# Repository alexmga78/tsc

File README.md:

# Engineering Validation (EVT) - PCB and Mechanical Design

## Project Overview

This project focuses on the design and validation of a printed circuit board (PCB) for an electronic device that includes various components like an ESP32-C6 module, battery, display, and mechanical housing. The goal is to ensure that the PCB fits within the given mechanical enclosure, adheres to specified electrical and mechanical constraints, and follows best practices for power routing, component placement, and design rules.

## Project Structure

- **Hardware**
  - **Schematic File** (`.sch`)
  - **PCB Layout File** (`.brd`)
- **Manufacturing**
  - **Gerbers** (`gerbers.zip`)
  - **Bill of Materials** (`.bom`)
  - **Pick and Place File** (`.cpl`)
- **Mechanical**
  - **3D Model of Complete Device** (exploded view `.step`)
  - **Fusion 360 3D Model** (assembled device)
- **Images**
  - Renders of the device, PCB, and individual components
- **LICENSE**
  - License information
- **README.md**
  - This file, describing the project

## Design Decisions and Functional Overview

### 1. **Schematic Design**
The schematic was designed according to the provided model and constraints. Key considerations included ensuring proper placement of decoupling capacitors close to the power pins of critical components, maintaining correct power and data routing widths, and keeping signal integrity intact.

- **Power Routing**: Power traces were routed with a minimum width of `0.3mm` for power rails (e.g., VCC, VBUS) and `0.15mm` for signal traces.
- **Component Placement**: All components were placed on the **TOP** layer of the PCB, with key modules grouped around the central ESP32-C6 microcontroller. The placement adhered to the mechanical dimensions of the housing.
- **Stacked Ground Planes**: Ground planes were created both on the **TOP** and **BOTTOM** layers, and via stitching was applied near the ESP32 module to ensure minimal noise.

### 2. **PCB Layout and Constraints**
Following the provided layout file, I ensured the PCB design adhered to all mechanical and electrical constraints, including:
- **Fitment with Housing**: The PCB was designed to fit inside the provided mechanical enclosure, and critical components such as buttons and USB connectors were positioned as per the specified dimensions.
- **ESP32 Antenna**: The antenna of the ESP32 module was placed near the outer edge of the PCB, and the area beneath it was cut out to minimize interference with the radio signal.
- **Double-sided Routing**: While routing was done on both the **TOP** and **BOTTOM** layers, I avoided vias on power traces and ensured that no signals were routed under the ESP32 antenna.
  
### 3. **Gerber Files**
Gerber files were generated to provide the necessary information for PCB manufacturing. I used the standard process outlined in the provided tutorial to generate the following:
- **Gerber Files** for PCB manufacturing
- **Bill of Materials** (BOM) for procurement
- **Pick and Place File** for component placement during assembly

### 4. **Mechanical Model**
The 3D model of the complete device, including the PCB, battery, display, and housing, was created in Fusion 360. The exploded view `.step` file shows the assembly process and how the components fit within the housing. The models for the battery and display were drawn according to their respective datasheets to ensure accurate dimensions.

- **Battery and Display Integration**: The battery was directly connected to the PCB's test pads, and the display was integrated according to its specified connections.

## Design Rule Check (DRC) and Electrical Rule Check (ERC)

The design was thoroughly checked using the DRC and ERC files provided in the project resources. All electrical and mechanical design constraints were respected, and the following issues were resolved:
- **Power trace widths** and **component placement** were validated.
- **Test pads** were clearly marked in the silkscreen layer with their corresponding signal names (e.g., MISO, MOSI, GND).
- **Via stitching** was applied to ensure proper grounding, particularly around the ESP32 module.

### 5. **Components Used in Mechanical and Electrical Integration**

The following key components were integrated into the design, both electrically on the PCB and mechanically within the Fusion 360 model. Each part was selected based on its functionality, size constraints, and compatibility with the ESP32-C6 ecosystem.

#### **Microcontroller Unit (MCU)**
- **ESP32-C6-WROOM-1-N1 (U2)**  
  A high-performance wireless module with integrated Wi-Fi and Bluetooth LE capabilities. This module acts as the central processing unit, managing connectivity, data handling, and control tasks for the entire device.

#### **Power Supply and Management**
- **USB-C Connector**  
  Primary power input for the device, allowing both power delivery and data communication.
- **LDO Voltage Regulator – XC6220A331MR-G (IC4)**  
  Ensures stable voltage for sensitive components, converting input power to regulated 3.3V.
- **Battery Charging IC – MCP73831**  
  Handles safe charging of a single-cell Li-Po battery, enabling portable operation.
- **Fuel Gauge – MAX17048G+T10 (U4)**  
  Monitors battery voltage and provides state-of-charge estimation for accurate power management.

#### **Memory and Data Storage**
- **External NOR Flash – W25Q512JVEIQ (U1)**  
  Non-volatile memory used to store logs, firmware updates, or configuration data.
- **MicroSD Card Slot**  
  Provides removable storage capability, useful for storing larger datasets or logs.

#### **Real-Time Clock (RTC)**
- **RTC Module – DS3231SN (U3)**  
  Maintains accurate timekeeping, even during power loss. A supercapacitor (C10) is included to retain time data temporarily when external power is disconnected.

#### **Environmental Sensing**
- **BME688 Sensor**  
  Measures temperature, humidity, pressure, and gas, providing rich environmental data for various applications.

#### **User Interface**
- **E-Paper Display**  
  A low-power screen for displaying information clearly and efficiently. Connected via a flat flex connector (`FH34SR-24S-0.5SH_99`) and supported by driver circuitry on the PCB.
- **Buttons (Boot, Reset, Change)**  
  Physical interface elements allowing users to interact with the system, perform resets, or trigger mode changes.

#### **Communication Interfaces**
- **Wireless Connectivity via ESP32-C6**  
  Native support for Wi-Fi 6 and Bluetooth LE enables fast, efficient communication with external devices or networks.

#### **Protection and Debugging**
- **ESD Protection – USBLC6-2SC6Y, PEMF050.1**  
  Safeguards sensitive components against electrostatic discharge from USB or other user-accessible interfaces.
- **Test Pads**  
  Strategically placed signal pads facilitate in-circuit testing and debugging during development or production.

#### **Expandability**
- **Qwiic/Stemma QT Connector**  
  Provides a plug-and-play I2C expansion port for easily integrating additional sensors or peripherals.

### 6. **MCU ESP32 Pins**

The ESP32-C6-WROOM-1 module was integrated as the core processing and communication unit. Its pinout was utilized to support a range of subsystems within the device. The following is an overview of how specific pins were used and organized in the design:

#### **Antenna Placement**
The ESP32-C6 features an integrated PCB antenna located at the end of the module. In this design, the antenna was placed along the outer edge of the PCB to maximize RF performance. A cutout was added beneath the antenna to reduce signal interference from copper traces or ground planes, ensuring reliable wireless communication.

#### **Power Pins**
- `3V3` and `GND` pins were used to supply and stabilize power to the ESP32 module.
- Proper decoupling capacitors were placed near these pins to minimize voltage fluctuations.

#### **USB Communication**
- USB data lines (`D+`, `D−`) were routed to the USB-C connector through ESD protection components, enabling USB-based programming and power delivery.

#### **SD Card Interface**
- Pins such as `CMD`, `CLK`, and `DAT0–DAT2` were connected to the MicroSD card slot to support external storage over an SDIO interface.

#### **SPI Communication**
- The SPI bus (`CS`, `SCK`, `MOSI`, `MISO`) was connected to the external flash memory (W25Q512JVEIQ) for fast, non-volatile storage access.

#### **I2C Bus**
- Two dedicated pins (`SDA`, `SCL`) were used to establish I2C communication with peripherals like the RTC (DS3231SN), environmental sensor (BME688), and the Qwiic/Stemma QT expansion port.

#### **GPIO Usage**
- Multiple GPIOs were assigned to handle:
  - **User Inputs**: Buttons such as Boot, Reset, and Change.
  - **Display Control**: Interface signals for driving the E-Paper display.
  - **Debug/Test Access**: Certain unused GPIOs were routed to test pads for development and troubleshooting.

All unused or unassigned GPIOs were kept accessible where possible for future flexibility.

## Issues and Resolutions

During the design and validation process, the following issues were identified and addressed:
- **Issue**: Minor overlap errors in component placement near the USB and button area.
  - **Resolution**: These errors were ignored as per the project instructions, as they did not interfere with functionality or the overall fit of the components inside the housing.
- **Issue**: Antenna placement under components.
  - **Resolution**: The PCB was redesigned to ensure no components or traces were placed beneath the antenna, and the area was cut out as required.

## Conclusion

This project adheres to the design specifications provided, ensuring that all hardware components, such as the ESP32-C6, battery, display, and PCB, fit within the specified mechanical enclosure. The design respects electrical and mechanical constraints, ensuring proper functionality, ease of assembly, and minimal interference.

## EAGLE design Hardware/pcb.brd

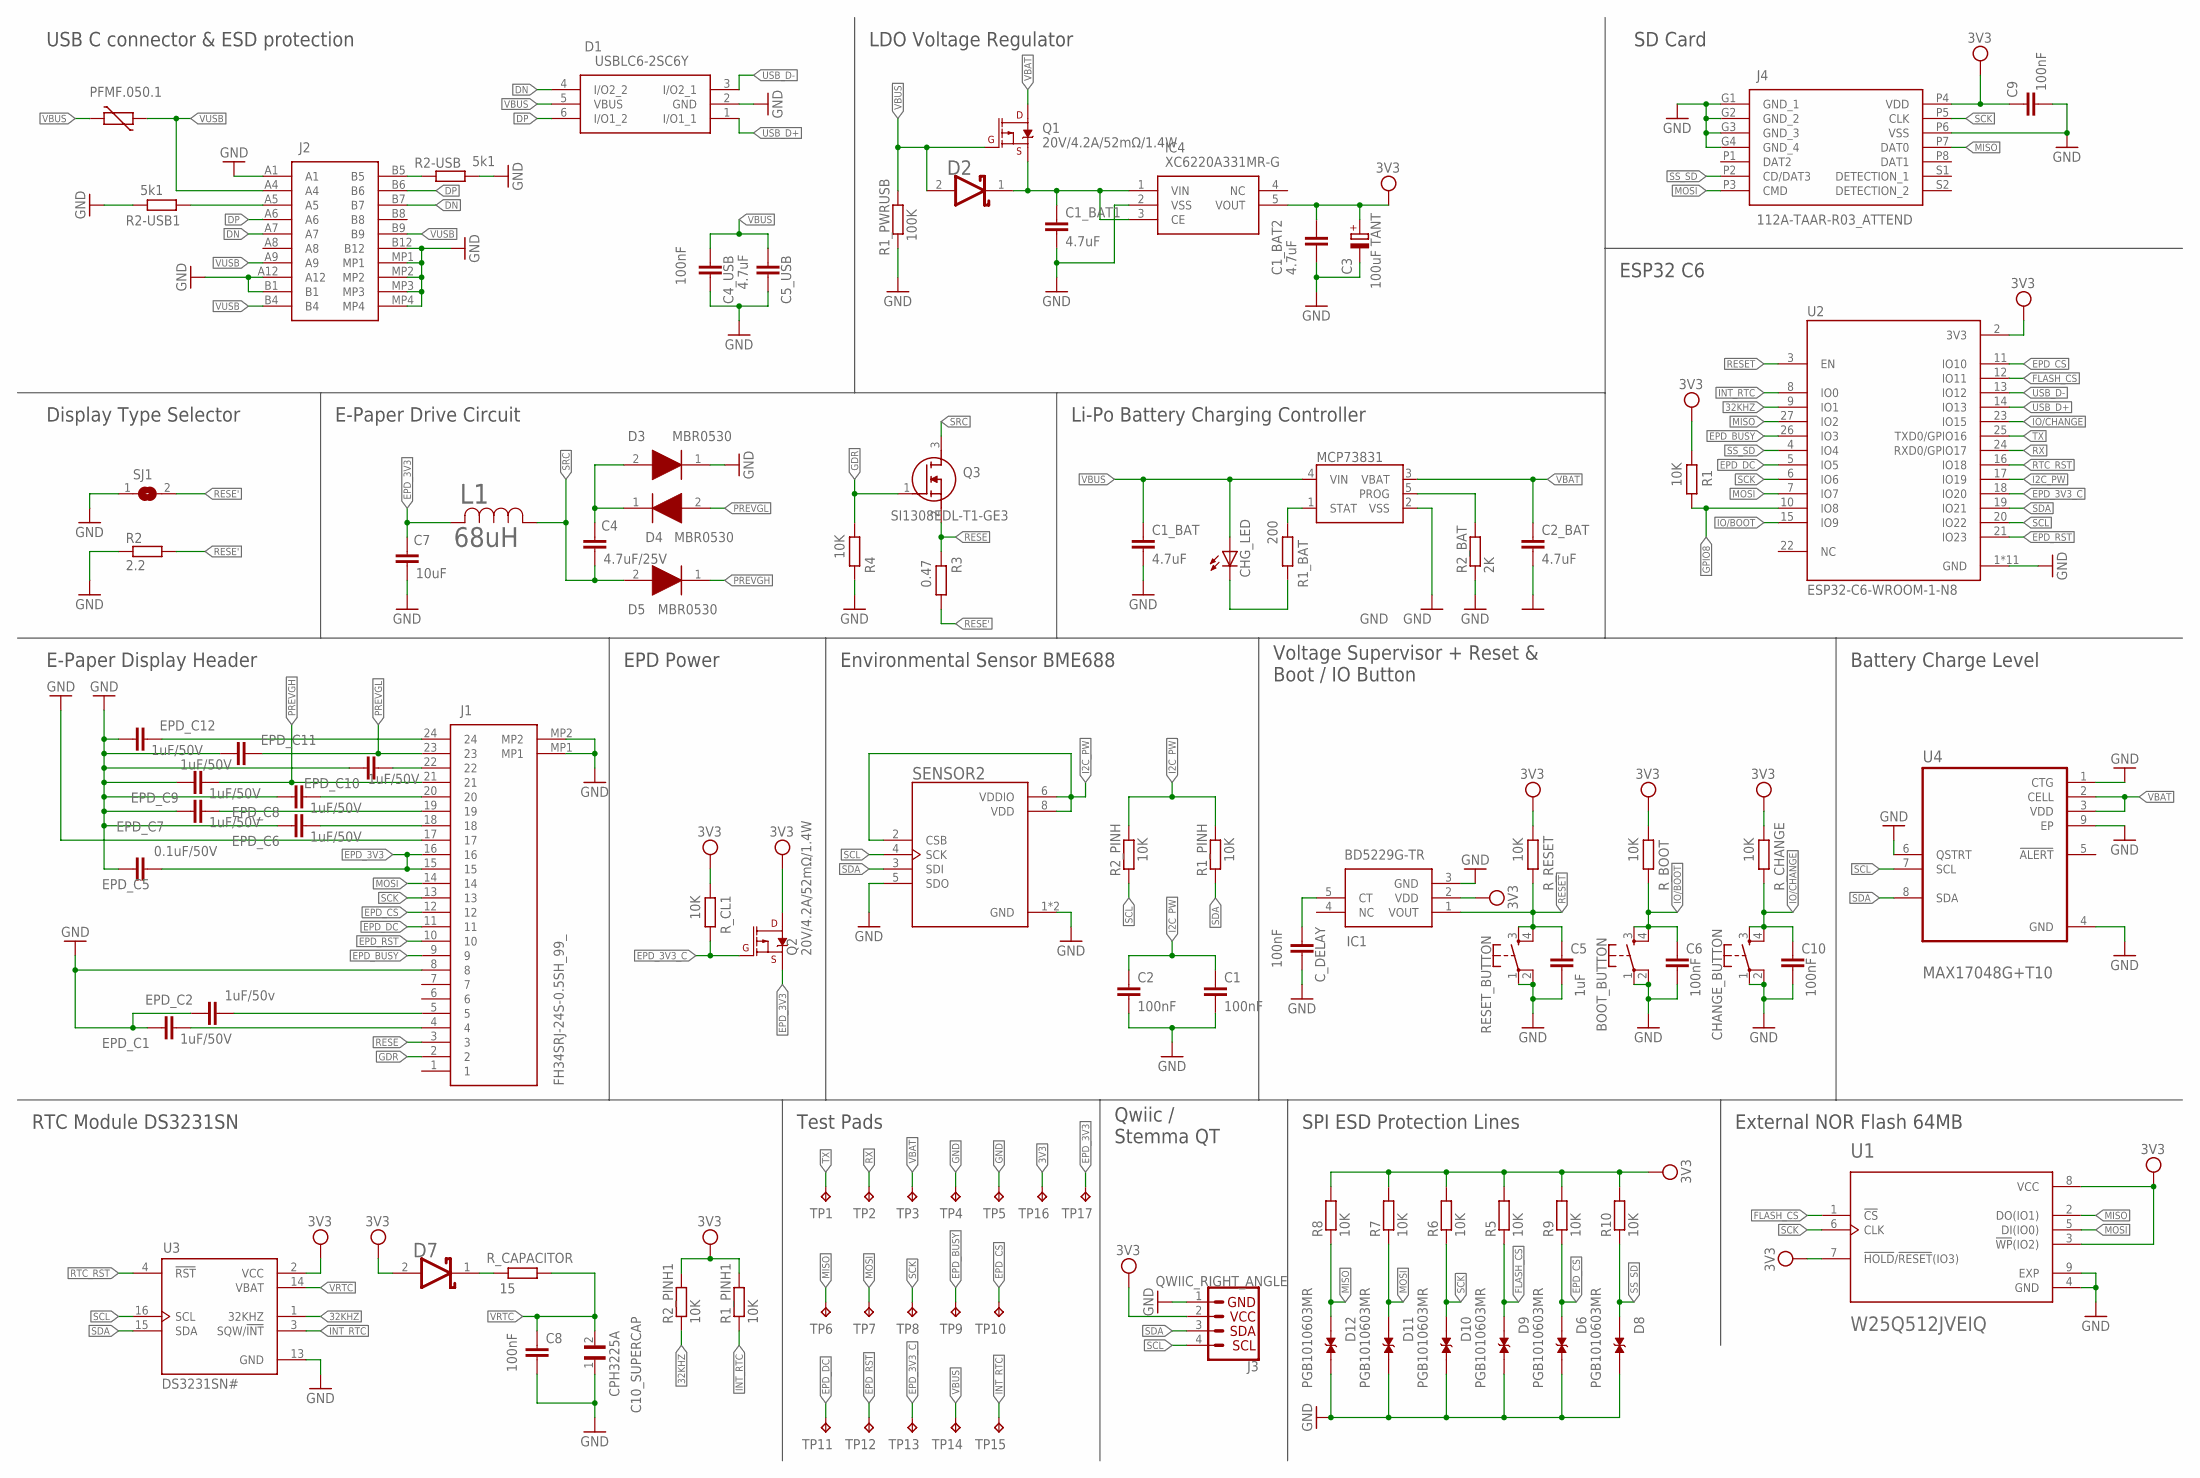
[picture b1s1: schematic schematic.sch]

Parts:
BOOT_BUTTON: BUTTON_CUSYOMV1; MYBUTTON
C1, C2, C6, C8, C9, C10: 100nF; ESP32_WROVER_EAGLE-LTSPICE_C0402
C1_BAT, C1_BAT1, C1_BAT2, C2_BAT: 4.7uF; ESP32_WROVER_EAGLE-LTSPICE_C0402
C3: 100uF TANT; RCL_CT3528
C4: 4.7uF/25V; EAGLE-LTSPICE_C0402
C4_USB: 100nF; EAGLE-LTSPICE_C0402
C5: 1uF; ESP32_WROVER_EAGLE-LTSPICE_C0402
C5_USB: 4.7uF; EAGLE-LTSPICE_C0402
C7: 10uF; EAGLE-LTSPICE_C0402
C10_SUPERCAP: CPH3225A; CAPCP3225X100N
CHANGE_BUTTON: BUTTON_CUSYOMV1; MYBUTTON
CHG_LED: ADAFRUIT_LEDCHIP-LED0603; ADAFRUIT_CHIP-LED0603
C_DELAY: 100nF; ESP32_WROVER_EAGLE-LTSPICE_C0402
D1: USBLC6-2SC6Y; SOT95P280X145-6N
D2, D7: ESP32_WROVER_AVX---SD0805S020S1R0_AVX_SD0805S020S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; ESP32_WROVER_AVX---SD0805S020S1R0_AVX_SD0805S020S1R0_0
D3, D4, D5: MBR0530; SOD3716X135N
D6, D8, D9, D10, D11, D12: PGB1010603MR; DIOC1608X36N
EPD_C1, EPD_C6, EPD_C7, EPD_C8, EPD_C9, EPD_C10, EPD_C11, EPD_C12: 1uF/50V; EAGLE-LTSPICE_C0402
EPD_C2: 1uF/50v; EAGLE-LTSPICE_C0402
EPD_C5: 0.1uF/50V; EAGLE-LTSPICE_C0402
IC1: BD5229G-TR; SOT95P280X125-5N
IC4: XC6220A331MR-G; SOT95P280X120-5N
J1: FH34SRJ-24S-0.5SH_99_; FH34SRJ24S05SH99
J2: SAMACSYS_PARTS_USB4110-GF-A; SAMACSYS_PARTS_USB4110GFA
J3: QWIIC_RIGHT_ANGLE; JST04_1MM_RA
J4: 112A-TAAR-R03_ATTEND; 112ATAARR03ATTEND
L1: 68uH; IND_4828-WE-TPC_WRE
MCP73831: ESP32_WROVER_SPARKFUN-IC-POWER_MCP73831; ESP32_WROVER_SPARKFUN-IC-POWER_SOT23-5
PFMF.050.1: ESP32C6_VARISTORCN1812; ESP32C6_VARISTOR_CT/CN1812
Q1, Q2: 20V/4.2A/52mΩ/1.4W; ESP32_WROVER_SPARKFUN-DISCRETESEMI_SOT23-3
Q3: SI1308EDL-T1-GE3; SOT65P210X110-3N
R1, R1_PINH, R1_PINH1, R2_PINH, R2_PINH1, R4, R5, R6, R7, R8, R9, R10: 10K; ESP32_WROVER_EAGLE-LTSPICE_R0402
R1_BAT: 200; ESP32_WROVER_EAGLE-LTSPICE_R0402
R1_PWRUSB: 100K; ESP32_WROVER_EAGLE-LTSPICE_R0402
R2: 2.2; ESP32_WROVER_EAGLE-LTSPICE_R0402
R2-USB, R2-USB1: 5k1; ESP32_WROVER_EAGLE-LTSPICE_R0402
R2_BAT: 2K; ESP32_WROVER_EAGLE-LTSPICE_R0402
R3: 0.47; ESP32_WROVER_EAGLE-LTSPICE_R0402
RESET_BUTTON: BUTTON_CUSYOMV1; MYBUTTON
R_BOOT: 10K; ESP32_WROVER_EAGLE-LTSPICE_R0402
R_CAPACITOR: 15; ESP32_WROVER_EAGLE-LTSPICE_R0402
R_CHANGE: 10K; ESP32_WROVER_EAGLE-LTSPICE_R0402
R_CL1: 10K; ESP32_WROVER_EAGLE-LTSPICE_R0402
R_RESET: 10K; ESP32_WROVER_EAGLE-LTSPICE_R0402
SENSOR2: ESP32_WROVER_BME680_BME680; ESP32_WROVER_BME680_PSON80P300X300X100-8N
SJ1: SJ
TP1, TP2, TP3, TP4, TP5, TP6, TP7, TP8, TP9, TP10, TP11, TP12, TP13, TP14, TP15, TP16, TP17: TPTP20R; TP20R
U1: W25Q512JVEIQ; SON127P600X800X80-9N
U2: ESP32-C6-WROOM-1-N8; XCVR_ESP32-C6-WROOM-1-N8
U3: DS3231SN#; SOIC127P1032X265-16N
U4: MAX17048G+T10; SON50P200X200X80-9N

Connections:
3V3: C1_BAT2.1, C3.+, C9.1, D7.2 (ANODE), IC1.2 (VDD), IC4.5 (VOUT), J3.2, J4.P4 (VDD), Q2.3 (D), R1.2, R1_PINH1.2, R2_PINH1.2, R5.2, R6.2, R7.2, R8.2, R9.2, R10.2, R_BOOT.2, R_CHANGE.2, R_CL1.2, R_RESET.2, TP16.TP, U1.3 (!WP!(IO2)), U1.7 (!HOLD!/!RESET!(IO3)), U1.8 (VCC), U2.2 (3V3), U3.2 (VCC)
32KHZ: R2_PINH1.1, U2.9 (IO1), U3.1 (32KHZ)
DN: D1.4 (I/O2_2), J2.A7, J2.B7
DP: D1.6 (I/O1_2), J2.A6, J2.B6
EPD_3V3: C7.1, EPD_C5.2, J1.15, J1.16, L1.2, Q2.2 (S), TP17.TP
EPD_3V3_C: Q2.1 (G), R_CL1.1, TP13.TP, U2.18 (IO20)
EPD_BUSY: J1.9, TP9.TP, U2.26 (IO3)
EPD_CS: D6.1, J1.12, R9.1, TP10.TP, U2.11 (IO10)
EPD_DC: J1.11, TP11.TP, U2.5 (IO5)
EPD_RST: J1.10, TP12.TP, U2.21 (IO23)
FLASH_CS: D9.1, R5.1, U1.1 (!CS), U2.12 (IO11)
GDR: J1.2, Q3.1 (G), R4.2
GND: BOOT_BUTTON.1, BOOT_BUTTON.2, C1.2, C1_BAT.2, C1_BAT1.2, C1_BAT2.2, C2.2, C2_BAT.2, C3.-, C4_USB.2, C5.2, C5_USB.2, C6.2, C7.2, C8.2, C9.2, C10.2, C10_SUPERCAP.1, CHANGE_BUTTON.1, CHANGE_BUTTON.2, C_DELAY.2, D1.2 (GND), D3.1 (K), D6.2, D8.2, D9.2, D10.2, D11.2, D12.2, EPD_C1.1, EPD_C2.1, EPD_C5.1, EPD_C6.1, EPD_C7.1, EPD_C8.1, EPD_C9.1, EPD_C10.1, EPD_C11.1, EPD_C12.1, IC1.3 (GND), IC4.2 (VSS), J1.8, J1.17, J1.MP1, J1.MP2, J2.A1, J2.A12, J2.B1, J2.B12, J2.MP1, J2.MP2, J2.MP3, J2.MP4, J3.1, J4.G1 (GND_1), J4.G2 (GND_2), J4.G3 (GND_3), J4.G4 (GND_4), J4.P6 (VSS), MCP73831.2 (VSS), R1_PWRUSB.1, R2.1, R2-USB.2, R2-USB1.1, R2_BAT.1, R4.1, RESET_BUTTON.1, RESET_BUTTON.2, SENSOR2.1 (GND), SENSOR2.5 (SDO), SENSOR2.7 (GND), SJ1.1, TP4.TP, TP5.TP, U1.4 (GND), U1.9 (EXP), U2.1 (GND), U2.28 (GND), U2.29_1 (GND), U2.29_2 (GND), U2.29_3 (GND), U2.29_4 (GND), U2.29_5 (GND), U2.29_6 (GND), U2.29_7 (GND), U2.29_8 (GND), U2.29_9 (GND), U3.13 (GND), U4.1 (CTG), U4.4 (GND), U4.6 (QSTRT), U4.9 (EP)
GPIO8: R1.1, U2.10 (IO8)
I2C_PW: C1.1, C2.1, R1_PINH.2, R2_PINH.2, SENSOR2.2 (CSB), SENSOR2.6 (VDDIO), SENSOR2.8 (VDD), U2.17 (IO19)
INT_RTC: R1_PINH1.1, TP15.TP, U2.8 (IO0), U3.3 (SQW/!INT)
IO/BOOT: BOOT_BUTTON.3, BOOT_BUTTON.4, C6.1, R_BOOT.1, U2.15 (IO9)
IO/CHANGE: C10.1, CHANGE_BUTTON.3, CHANGE_BUTTON.4, R_CHANGE.1, U2.23 (IO15)
MISO: D12.1, J4.P7 (DAT0), R8.1, TP6.TP, U1.2 (DO(IO1)), U2.27 (IO2)
MOSI: D11.1, J1.14, J4.P3 (CMD), R7.1, TP7.TP, U1.5 (DI(IO0)), U2.7 (IO7)
unnamed: J2.B5, R2-USB.1
unnamed: C4.1, D3.2 (A), D4.1 (K)
unnamed: C1_BAT1.1, D2.1 (CATHODE), IC4.1 (VIN), IC4.3 (CE), Q1.2 (S)
unnamed: EPD_C12.2, J1.24
unnamed: MCP73831.1 (STAT), R1_BAT.2
unnamed: CHG_LED.C, R1_BAT.1
unnamed: MCP73831.5 (PROG), R2_BAT.2
unnamed: C_DELAY.1, IC1.5 (CT)
unnamed: J2.A5, R2-USB1.2
unnamed: EPD_C10.2, J1.22
unnamed: D7.1 (CATHODE), R_CAPACITOR.2
unnamed: EPD_C8.2, J1.20
unnamed: EPD_C7.2, J1.19
unnamed: EPD_C6.2, J1.18
unnamed: EPD_C1.2, J1.4
unnamed: EPD_C2.2, J1.5
PREVGH: D5.1 (K), EPD_C9.2, J1.21
PREVGL: D4.2 (A), EPD_C11.2, J1.23
RESE: J1.3, Q3.2 (S), R3.2
RESE': R2.2, R3.1, SJ1.2
RESET: C5.1, IC1.1 (VOUT), RESET_BUTTON.3, RESET_BUTTON.4, R_RESET.1, U2.3 (EN)
RTC_RST: U2.16 (IO18), U3.4 (!RST)
RX: TP2.TP, U2.24 (RXD0/GPIO17)
SCK: D10.1, J1.13, J4.P5 (CLK), R6.1, TP8.TP, U1.6 (CLK), U2.6 (IO6)
SCL: J3.4, R2_PINH.1, SENSOR2.4 (SCK), U2.20 (IO22), U3.16 (SCL), U4.7 (SCL)
SDA: J3.3, R1_PINH.1, SENSOR2.3 (SDI), U2.19 (IO21), U3.15 (SDA), U4.8 (SDA)
SRC: C4.2, D5.2 (A), L1.1, Q3.3 (D)
SS_SD: D8.1, J4.P2 (CD/DAT3), R10.1, U2.4 (IO4)
TX: TP1.TP, U2.25 (TXD0/GPIO16)
USB_D+: D1.1 (I/O1_1), U2.14 (IO13)
USB_D-: D1.3 (I/O2_1), U2.13 (IO12)
VBAT: C2_BAT.1, MCP73831.3 (VBAT), Q1.3 (D), TP3.TP, U4.2 (CELL), U4.3 (VDD)
VBUS: C1_BAT.1, C4_USB.1, C5_USB.1, CHG_LED.A, D1.5 (VBUS), D2.2 (ANODE), MCP73831.4 (VIN), PFMF.050.1.2, Q1.1 (G), R1_PWRUSB.2, TP14.TP
VRTC: C8.1, C10_SUPERCAP.2, R_CAPACITOR.1, U3.14 (VBAT)
VUSB: J2.A4, J2.A9, J2.B4, J2.B9, PFMF.050.1.1

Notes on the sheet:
USB C connector & ESD protection
LDO Voltage Regulator
SD Card
ESP32 C6
Li-Po Battery Charging Controller
E-Paper Drive Circuit
Display Type Selector
E-Paper Display Header
EPD Power
Environmental Sensor BME688
Voltage Supervisor + Reset & Boot / IO Button
Battery Charge Level
External NOR Flash 64MB
SPI ESD Protection Lines
Qwiic / Stemma QT
Test Pads
RTC Module DS3231SN

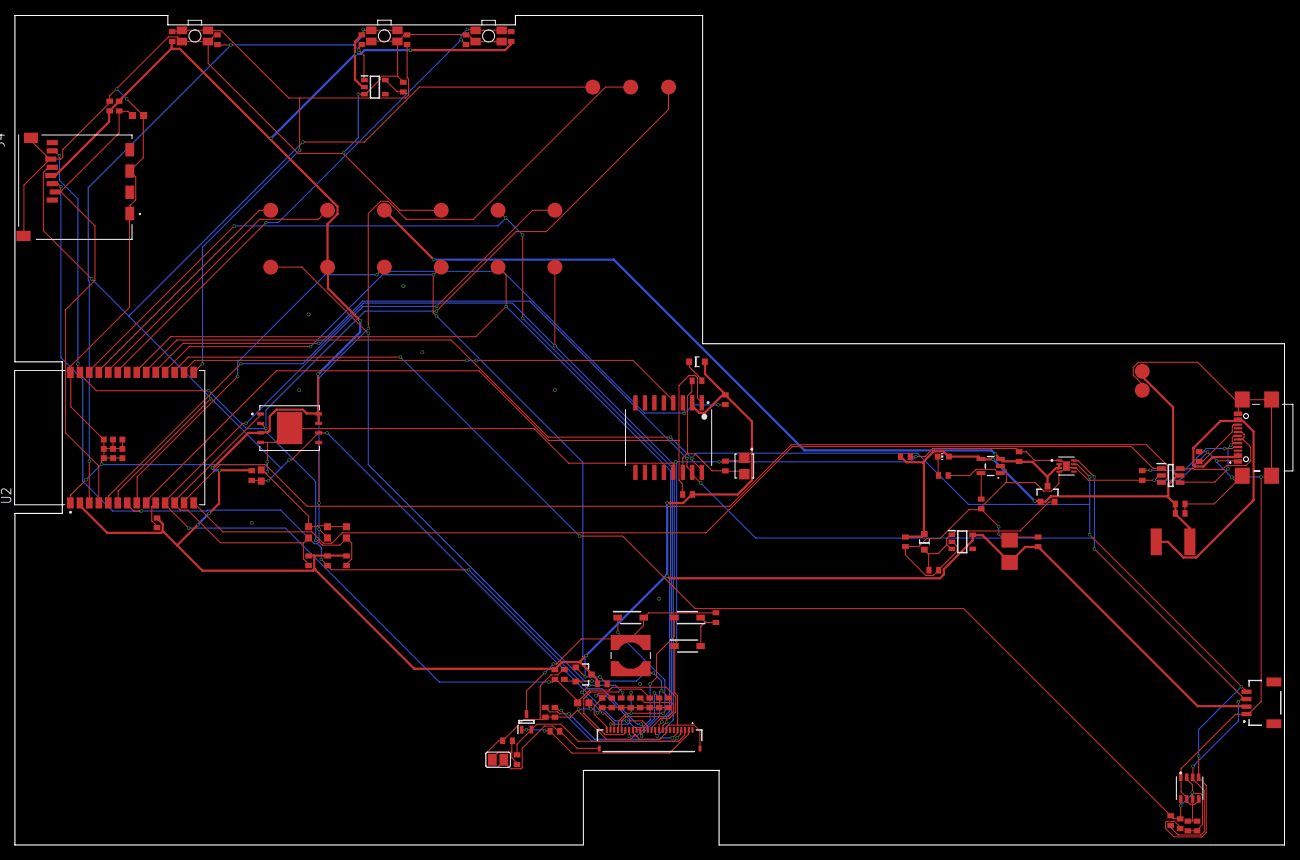
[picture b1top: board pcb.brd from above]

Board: 2 copper layers, 170.2 x 111.2 mm, 103 parts (0 on the bottom side), 55 nets.

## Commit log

2025-04-06 s-a terminat, doamne ajuta
2025-04-06 added LICENSE
2025-04-11 fixed review issues

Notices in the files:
parts and their libraries:
COPYRIGHT: Copyright (C) 2024 Ultra Librarian. All rights reserved.
